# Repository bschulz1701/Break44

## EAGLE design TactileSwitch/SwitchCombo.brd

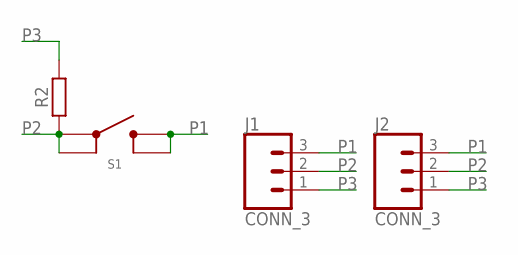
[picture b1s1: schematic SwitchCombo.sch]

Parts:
J1, J2: CONN_3; 1X03
R2: 10k; R_TH_0.4"
S1: BUTTON6X6_TH; SWITCH_6MM_TH

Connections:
P1: J1.3, J2.3, S1.3, S1.4
P2: J1.2, J2.2, R2.P$1 (1), S1.1, S1.2
P3: J1.1, J2.1, R2.P$2 (2)

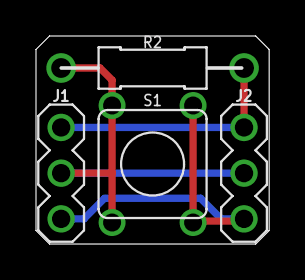
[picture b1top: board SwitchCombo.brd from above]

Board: 2 copper layers, 13.0 x 11.6 mm, 4 parts (0 on the bottom side), 3 nets.

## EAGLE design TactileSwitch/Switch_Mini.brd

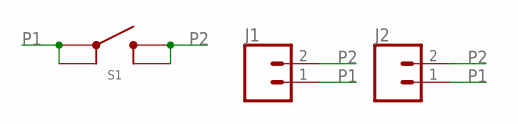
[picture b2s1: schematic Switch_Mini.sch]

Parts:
J1, J2: CONN_02; 1X02
S1: BUTTON4.2X3.2; SWITCH_4.2X3.2

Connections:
P1: J1.1, J2.1, S1.1, S1.2
P2: J1.2, J2.2, S1.3 (4), S1.4 (3)

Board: 2 copper layers, 3 parts (0 on the bottom side), 2 nets, no tracks yet.

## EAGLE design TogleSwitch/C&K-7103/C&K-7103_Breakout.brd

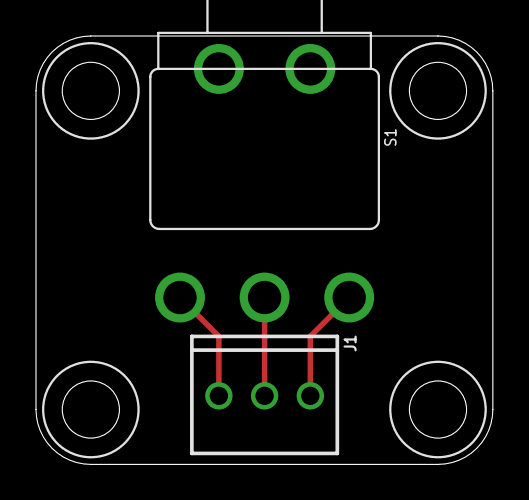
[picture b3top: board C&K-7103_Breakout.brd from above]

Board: 2 copper layers, 25.4 x 23.8 mm, 6 parts (0 on the bottom side), 3 nets.

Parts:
H1, H2, H3, H4: 4_40
J1: CONN_32.54_SCREW; 1X03_SCREW
S1: SPDT7103K2CWA; 7103K2CWA

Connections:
P1: J1.3, S1.1
P2: J1.1, S1.3
S: J1.2, S1.2

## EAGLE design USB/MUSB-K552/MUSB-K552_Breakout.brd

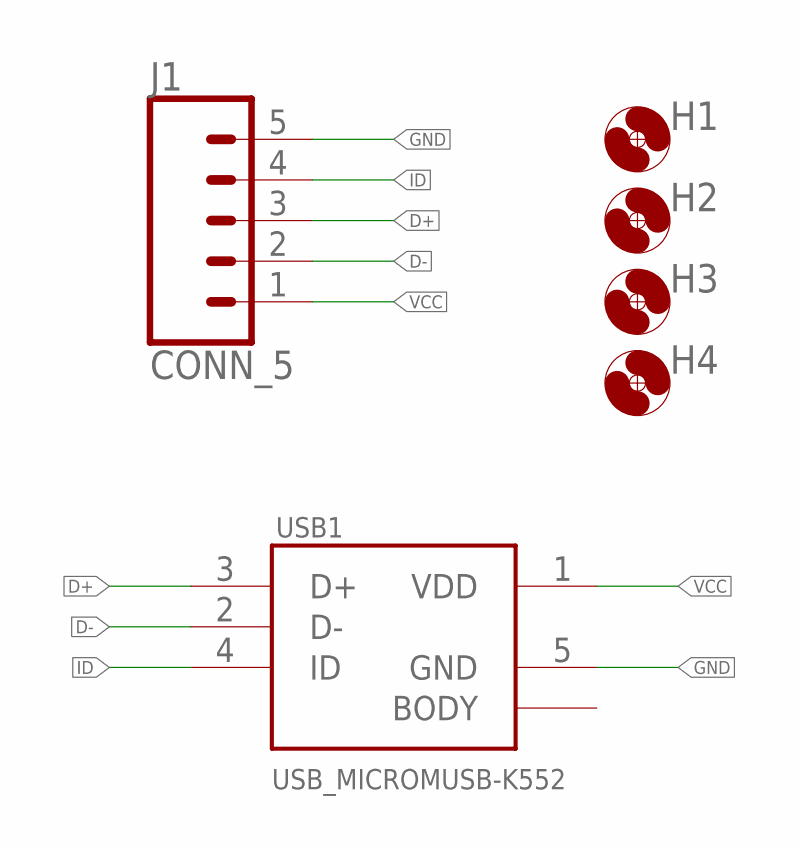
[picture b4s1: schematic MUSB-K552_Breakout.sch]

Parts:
H1, H2, H3, H4: MOUNTING_HOLE2_NP; 2_56
J1: CONN_5; 1X05
USB1: USB_MICROMUSB-K552; MUSB-K552-30

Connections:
D+: J1.3, USB1.3 (D+)
D-: J1.2, USB1.2 (D-)
GND: J1.5, USB1.5 (GND)
ID: J1.4, USB1.4 (ID)
VCC: J1.1, USB1.1 (VDD)

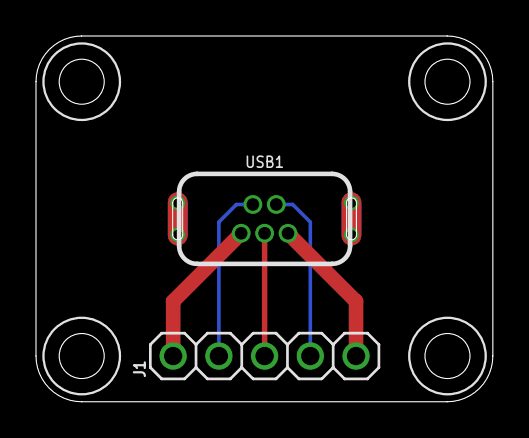
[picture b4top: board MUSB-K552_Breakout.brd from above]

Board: 2 copper layers, 25.4 x 20.3 mm, 6 parts (0 on the bottom side), 5 nets.

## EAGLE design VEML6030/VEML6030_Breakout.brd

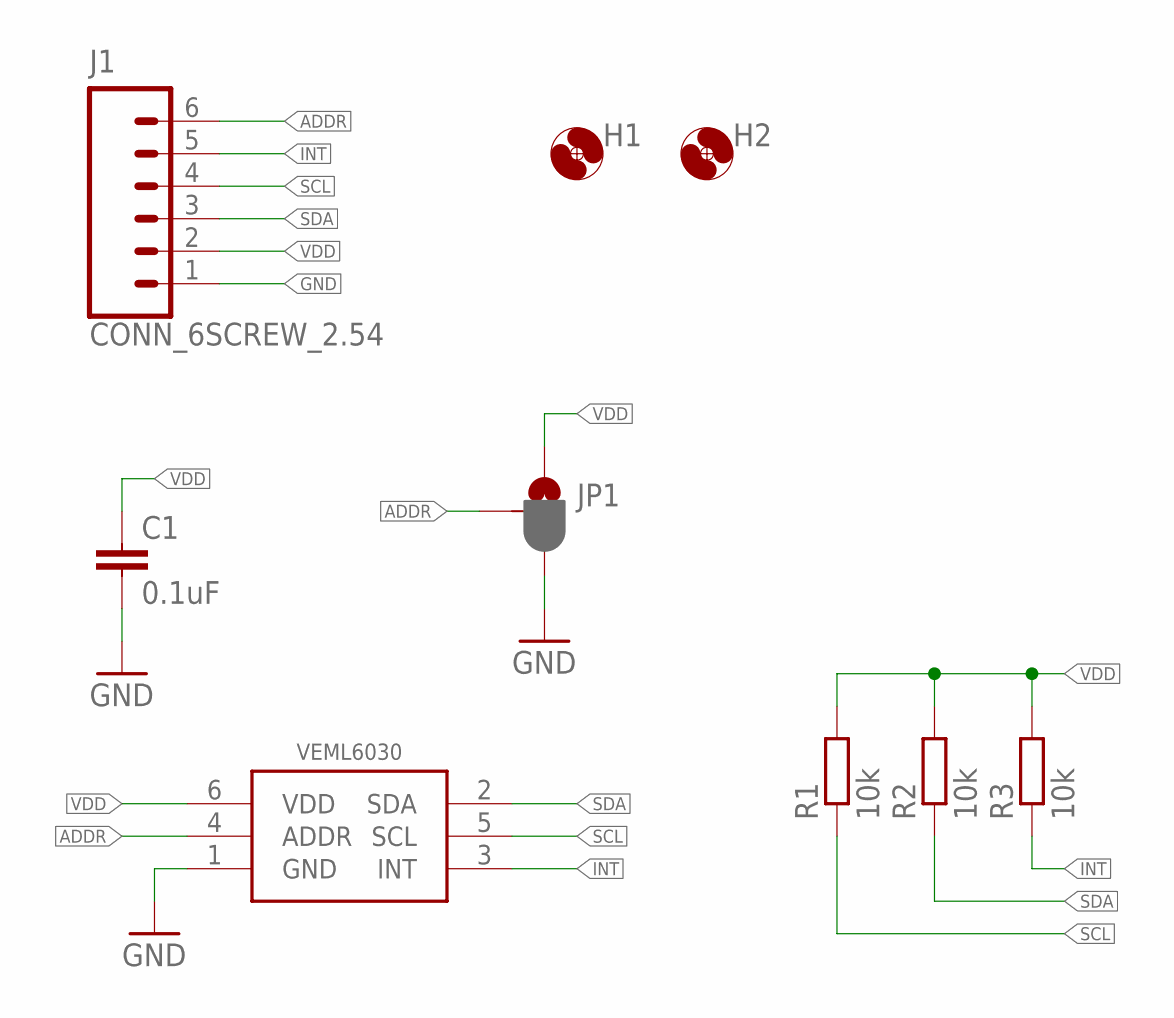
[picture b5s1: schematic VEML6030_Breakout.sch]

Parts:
C1: 0.1uF; C0603
H1, H2: MOUNTING_HOLE2_NP; 2_56
J1: CONN_6SCREW_2.54; 1X06_SCREW
JP1: JUMPER-SMT_3_1-NC_PASTE_SILK; SMT-JUMPER_3_1-NC_PASTE_SILK
R1, R2, R3: 10k; R0603
U1: VEML6030

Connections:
ADDR: J1.6, JP1.2, U1.4 (ADDR)
GND: C1.2, J1.1, JP1.3, U1.1 (GND)
INT: J1.5, R3.1, U1.3 (INT)
SCL: J1.4, R1.1, U1.5 (SCL)
SDA: J1.3, R2.1, U1.2 (SDA)
VDD: C1.1, J1.2, JP1.1, R1.2, R2.2, R3.2, U1.6 (VDD)

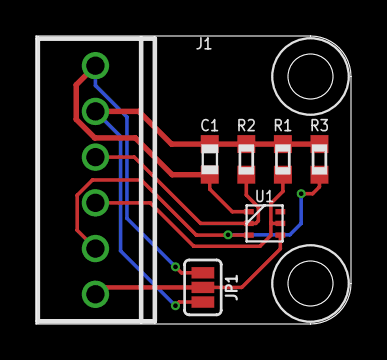
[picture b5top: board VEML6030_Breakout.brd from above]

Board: 2 copper layers, 17.5 x 16.0 mm, 9 parts (0 on the bottom side), 6 nets.

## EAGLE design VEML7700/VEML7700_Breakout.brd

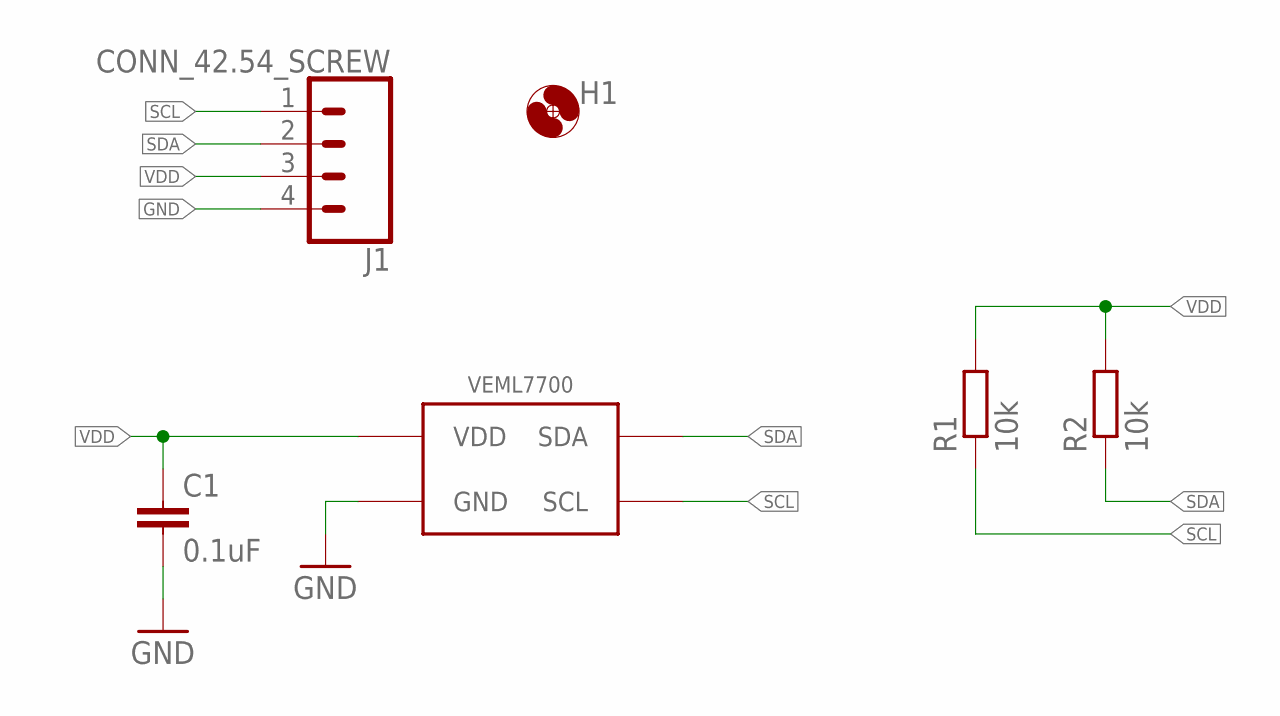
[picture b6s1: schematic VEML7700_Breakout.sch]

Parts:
C1: 0.1uF; C0603
H1: MOUNTING_HOLE2_NP; 2_56
J1: CONN_42.54_SCREW; 1X04_SCREW
R1, R2: 10k; R0603
U1: VEML7700

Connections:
GND: C1.2, J1.4, U1.3 (GND)
SCL: J1.1, R1.1, U1.1 (SCL)
SDA: J1.2, R2.1, U1.4 (SDA)
VDD: C1.1, J1.3, R1.2, R2.2, U1.2 (VDD)

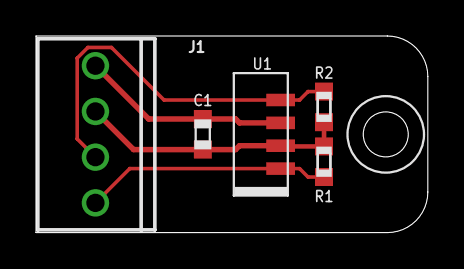
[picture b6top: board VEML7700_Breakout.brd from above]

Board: 2 copper layers, 21.8 x 10.9 mm, 6 parts (0 on the bottom side), 4 nets.

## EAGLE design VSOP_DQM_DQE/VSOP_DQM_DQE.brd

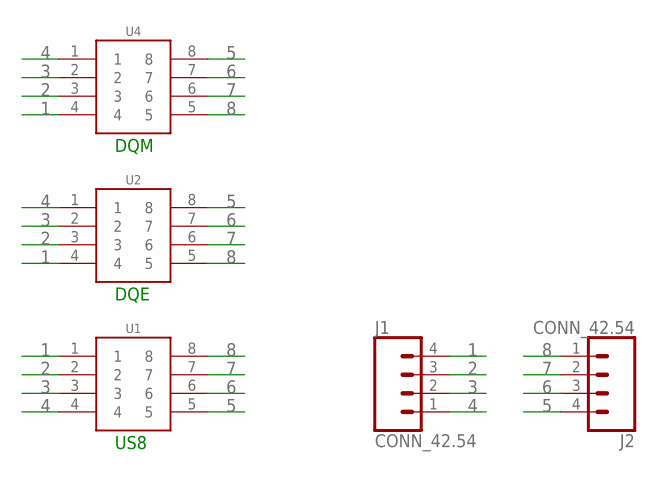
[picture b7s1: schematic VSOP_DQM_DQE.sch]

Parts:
J1, J2: CONN_42.54; 1X04
U1: GEN_8VSOP; DCU_(R-PDSO-G8)
U2: GEN_8DQE; DQE_R-PX2SON-N8
U4: GEN_8DQM; DQM_R-PX2SON-N8

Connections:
1: J1.4, U1.1, U2.4, U4.4
2: J1.3, U1.2, U2.3, U4.3
3: J1.2, U1.3, U2.2, U4.2
4: J1.1, U1.4, U2.1, U4.1
5: J2.4, U1.5, U2.8, U4.8
6: J2.3, U1.6, U2.7, U4.7
7: J2.2, U1.7, U2.6, U4.6
8: J2.1, U1.8, U2.5, U4.5

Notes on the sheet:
DQE
US8
DQM

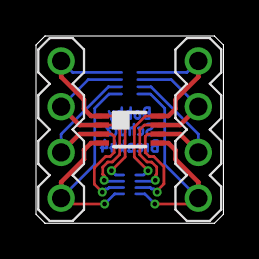
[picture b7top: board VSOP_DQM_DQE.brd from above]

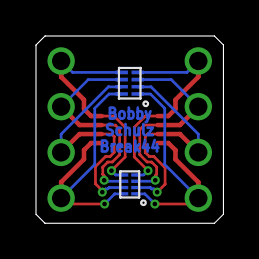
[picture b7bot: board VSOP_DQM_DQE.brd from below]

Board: 2 copper layers, 10.4 x 10.4 mm, 5 parts (2 on the bottom side), 8 nets.
